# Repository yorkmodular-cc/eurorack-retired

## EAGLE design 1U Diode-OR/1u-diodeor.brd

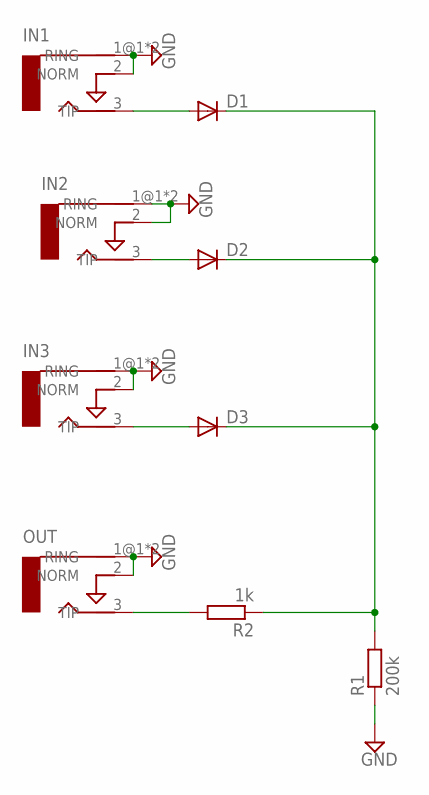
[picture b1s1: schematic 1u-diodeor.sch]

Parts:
D1, D2, D3: DIODE-SOD123; SOD123
IN1, IN2, IN3: AUDIO-JACKERTHENVAR; ERTHENVAR-JACK
OUT: AUDIO-JACKERTHENVAR; ERTHENVAR-JACK
R1: 200k; R0805
R2: 1k; R0805

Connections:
GND: IN1.1@1 (RING), IN1.1@2 (RING), IN1.2 (NORM), IN2.1@1 (RING), IN2.1@2 (RING), IN2.2 (NORM), IN3.1@1 (RING), IN3.1@2 (RING), IN3.2 (NORM), OUT.1@1 (RING), OUT.1@2 (RING), OUT.2 (NORM), R1.1
unnamed: D1.A, IN1.3 (TIP)
unnamed: D2.A, IN2.3 (TIP)
unnamed: D3.A, IN3.3 (TIP)
unnamed: D1.C, D2.C, D3.C, R1.2, R2.1
unnamed: OUT.3 (TIP), R2.2

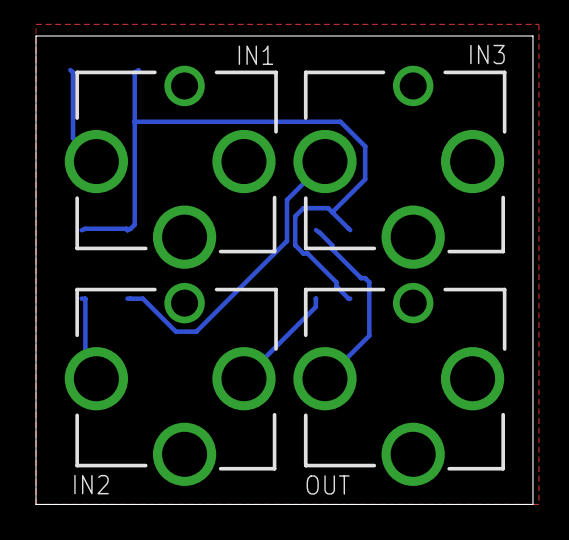
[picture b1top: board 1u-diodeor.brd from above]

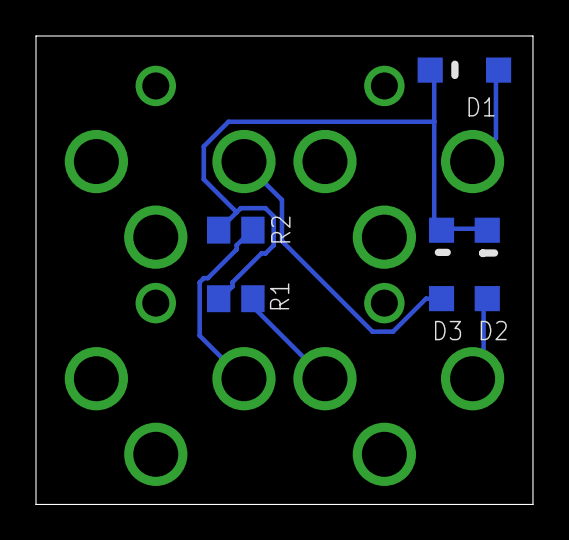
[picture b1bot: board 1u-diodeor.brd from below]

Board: 2 copper layers, 27.6 x 26.0 mm, 9 parts (5 on the bottom side), 6 nets.

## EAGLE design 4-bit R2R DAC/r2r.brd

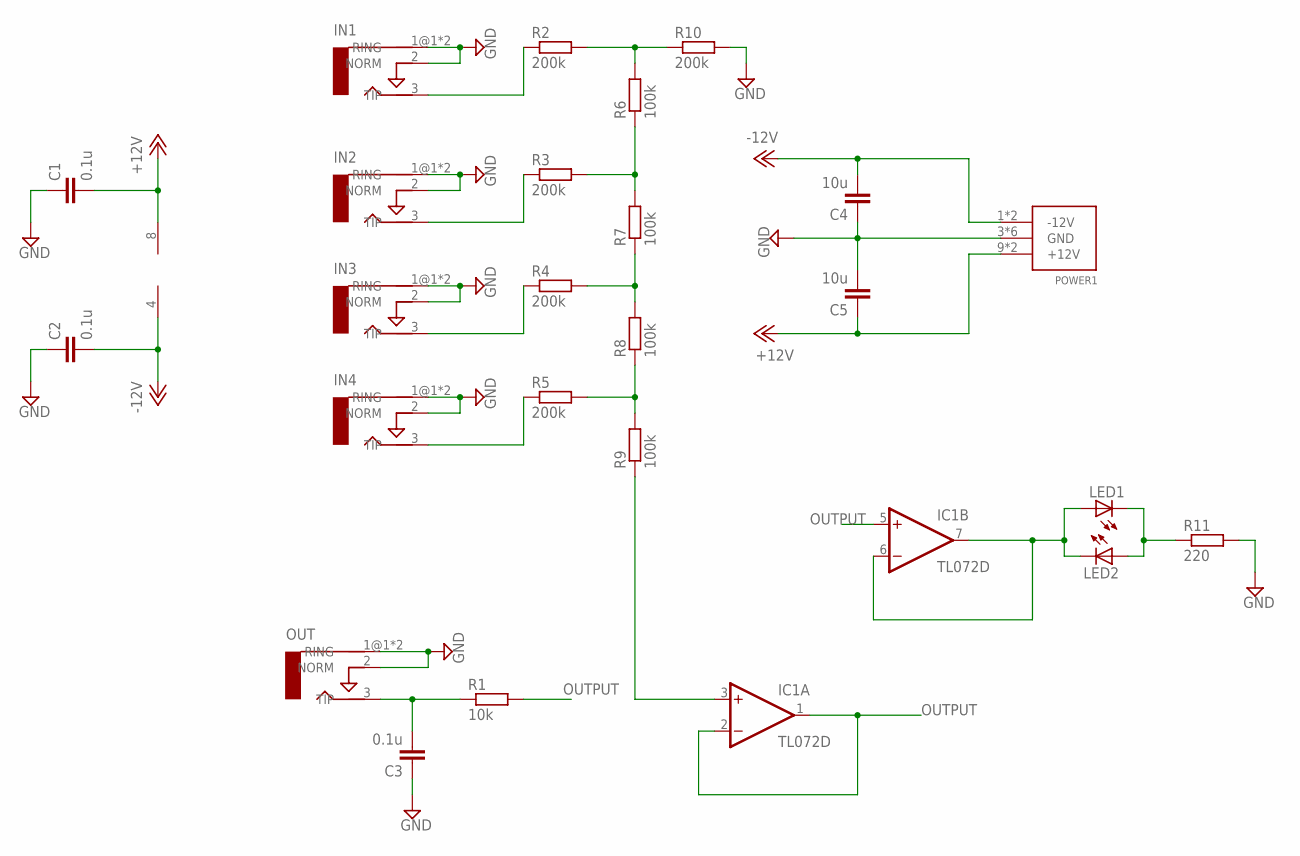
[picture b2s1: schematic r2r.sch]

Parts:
C1, C2, C3: 0.1u; C0805
C4, C5: 10u; C0805
IC1: TL072D; SO08
IN1, IN2, IN3, IN4: AUDIO-JACKERTHENVAR; ERTHENVAR-JACK
LED1, LED2: LEDCHIP-LED0805; CHIP-LED0805
OUT: AUDIO-JACKERTHENVAR; ERTHENVAR-JACK
POWER1: POWER_SIMPLE10; POWER_10
R1: 10k; R0805
R2, R3, R4, R5, R10: 200k; R0805
R6, R7, R8, R9: 100k; R0805
R11: 220; R0805

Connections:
+12V: C1.2, C5.1, IC1.8 (V+), POWER1.9 (+12V), POWER1.10 (+12V)
-12V: C2.2, C4.2, IC1.4 (V-), POWER1.1 (-12V), POWER1.2 (-12V)
GND: C1.1, C2.1, C3.1, C4.1, C5.2, IN1.1@1 (RING), IN1.1@2 (RING), IN1.2 (NORM), IN2.1@1 (RING), IN2.1@2 (RING), IN2.2 (NORM), IN3.1@1 (RING), IN3.1@2 (RING), IN3.2 (NORM), IN4.1@1 (RING), IN4.1@2 (RING), IN4.2 (NORM), OUT.1@1 (RING), OUT.1@2 (RING), OUT.2 (NORM), POWER1.3 (GND), POWER1.4 (GND), POWER1.5 (GND), POWER1.6 (GND), POWER1.7 (GND), POWER1.8 (GND), R10.2, R11.2
unnamed: IN1.3 (TIP), R2.1
unnamed: R2.2, R6.2, R10.1
unnamed: IN2.3 (TIP), R3.1
unnamed: R3.2, R6.1, R7.2
unnamed: IC1.3 (+IN), R9.1
unnamed: R5.2, R8.1, R9.2
unnamed: R4.2, R7.1, R8.2
unnamed: IN3.3 (TIP), R4.1
unnamed: IN4.3 (TIP), R5.1
unnamed: LED1.C, LED2.A, R11.1
unnamed: C3.2, OUT.3 (TIP), R1.1
unnamed: IC1.6 (-IN), IC1.7 (OUT), LED1.A, LED2.C
OUTPUT: IC1.1 (OUT), IC1.2 (-IN), IC1.5 (+IN), R1.2

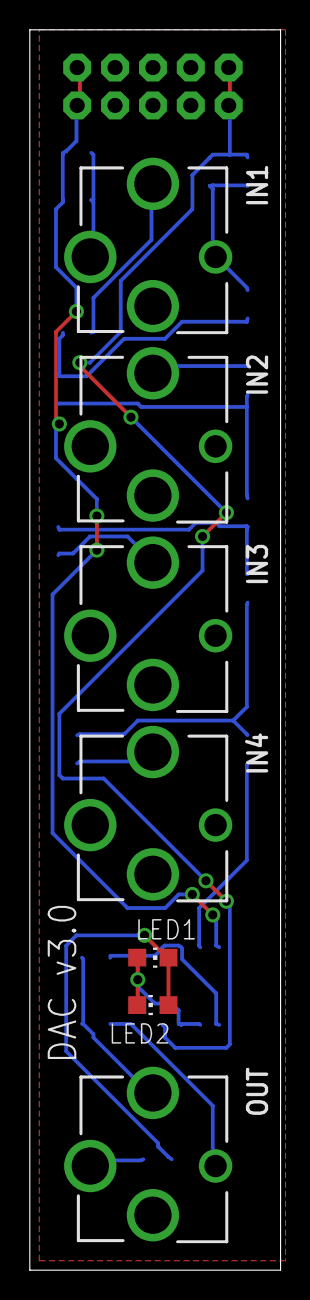
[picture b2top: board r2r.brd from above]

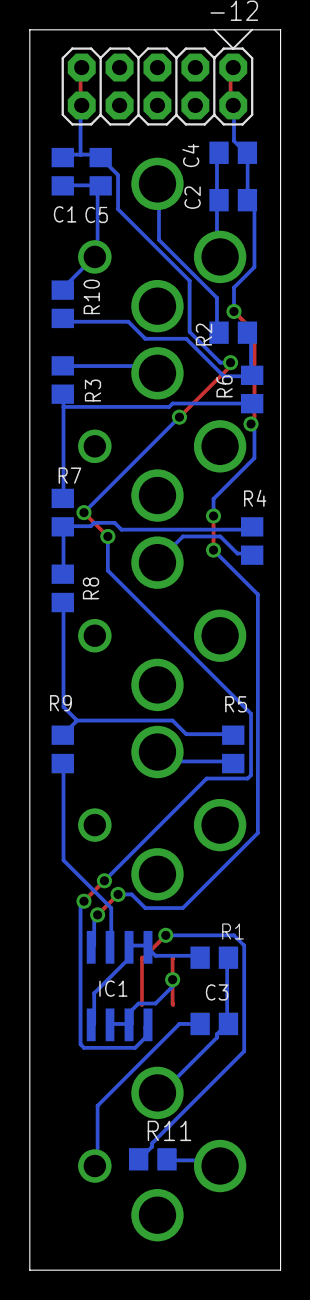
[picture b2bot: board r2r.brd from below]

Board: 2 copper layers, 16.8 x 83.2 mm, 25 parts (18 on the bottom side), 16 nets.

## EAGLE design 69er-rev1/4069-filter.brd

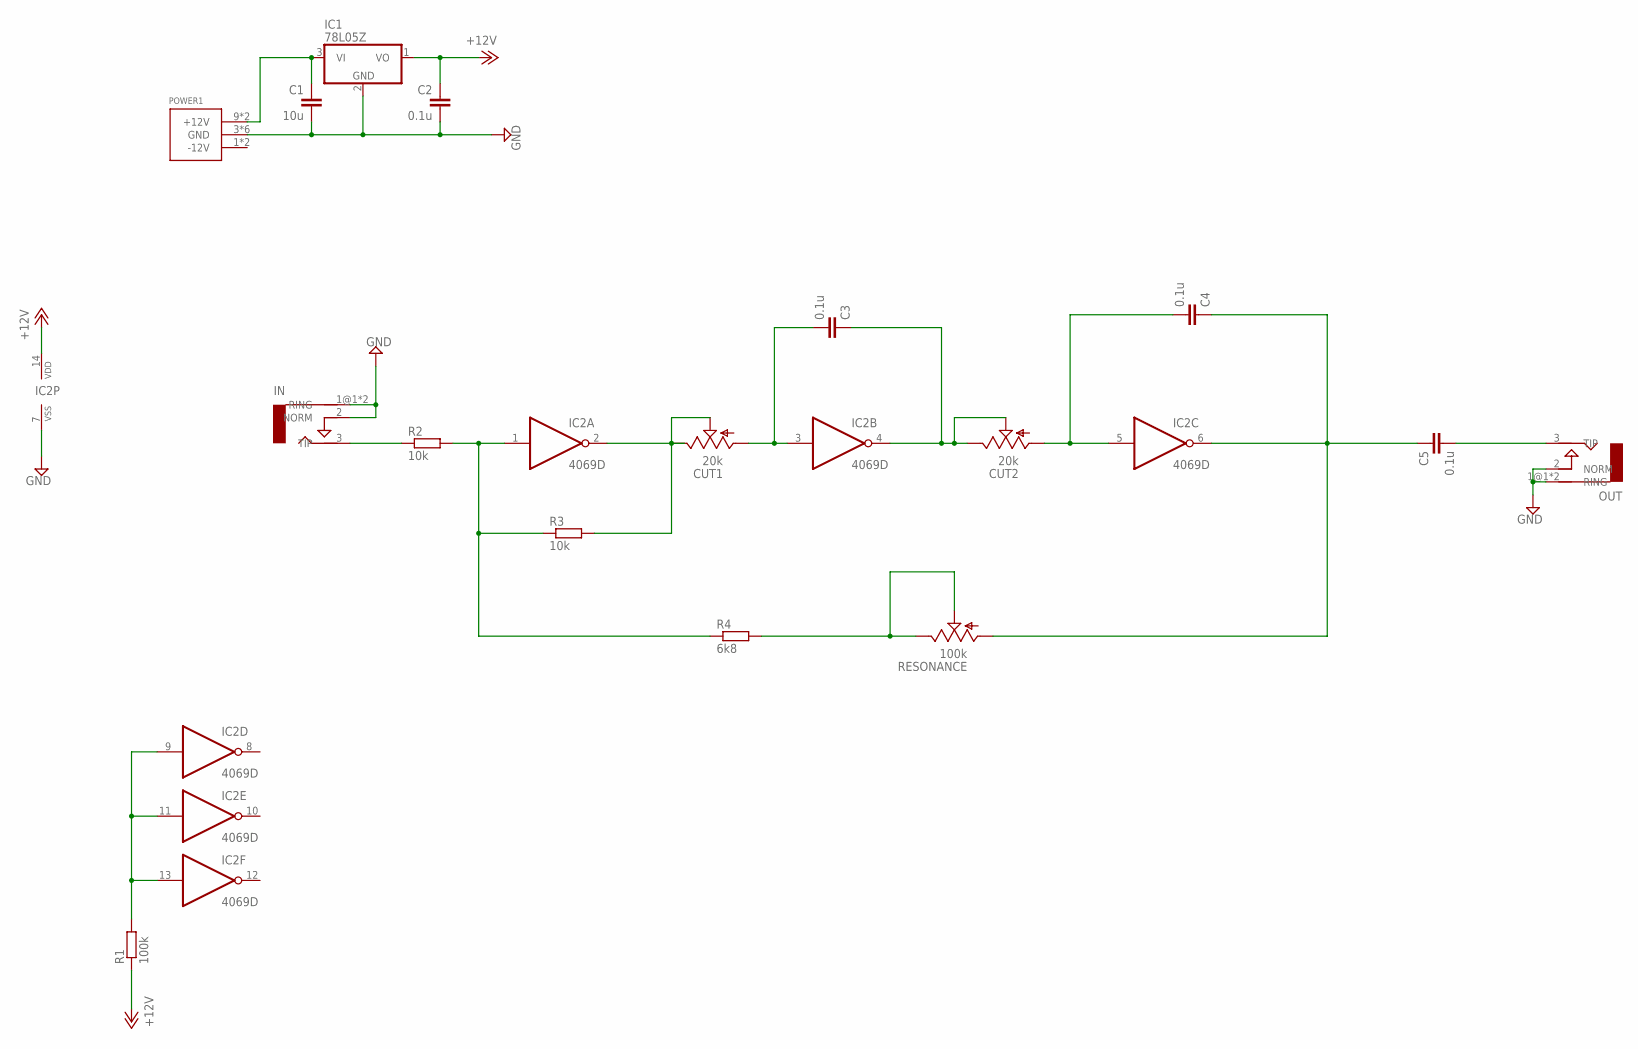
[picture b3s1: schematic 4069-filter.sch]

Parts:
C1: 10u; C0805
C2, C3, C4, C5: 0.1u; C0805
CUT1, CUT2: 20k; 9MM_SNAP-IN_POT
IC1: 78L05Z; TO92
IC2: 4069D; SO14
IN: AUDIO-JACKERTHENVAR; ERTHENVAR-JACK
OUT: AUDIO-JACKERTHENVAR; ERTHENVAR-JACK
POWER1: POWER_SIMPLE10; POWER_10
R1: 100k; R0805
R2, R3: 10k; R0805
R4: 6k8; R0805
RESONANCE: 100k; 9MM_SNAP-IN_POT

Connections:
+12V: C2.1, IC1.1 (VO), IC2.14 (VDD), R1.1
FILTER_OUT1: C3.1, CUT2.2 (S), CUT2.3 (E), IC2.4 (O)
FILTER_OUT2: C4.1, C5.1, IC2.6 (O), RESONANCE.1 (A)
GND: C1.2, C2.2, IC1.2 (GND), IC2.7 (VSS), IN.1@1 (RING), IN.1@2 (RING), IN.2 (NORM), OUT.1@1 (RING), OUT.1@2 (RING), OUT.2 (NORM), POWER1.3 (GND), POWER1.4 (GND), POWER1.5 (GND), POWER1.6 (GND), POWER1.7 (GND), POWER1.8 (GND)
IN: IN.3 (TIP), R2.1
unnamed: C5.2, OUT.3 (TIP)
unnamed: IC2.9 (I), IC2.11 (I), IC2.13 (I), R1.2
unnamed: C1.1, IC1.3 (VI), POWER1.9 (+12V), POWER1.10 (+12V)
unnamed: C3.2, CUT1.1 (A), IC2.3 (I)
unnamed: C4.2, CUT2.1 (A), IC2.5 (I)
unnamed: R4.2, RESONANCE.2 (S), RESONANCE.3 (E)
unnamed: CUT1.2 (S), CUT1.3 (E), IC2.2 (O), R3.2
unnamed: IC2.1 (I), R2.2, R3.1, R4.1

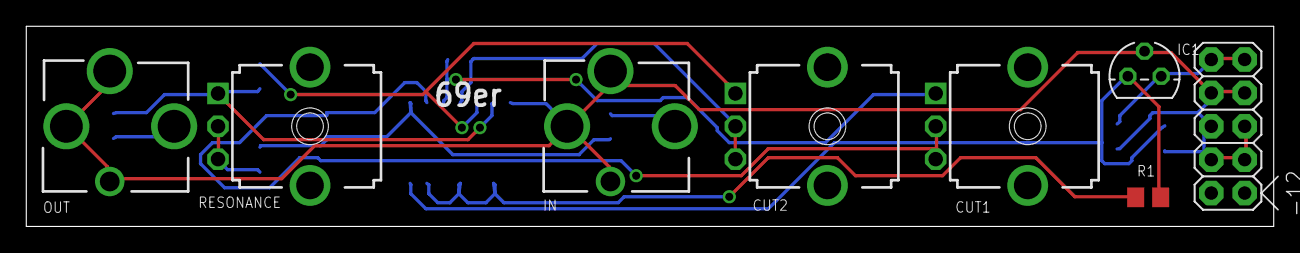
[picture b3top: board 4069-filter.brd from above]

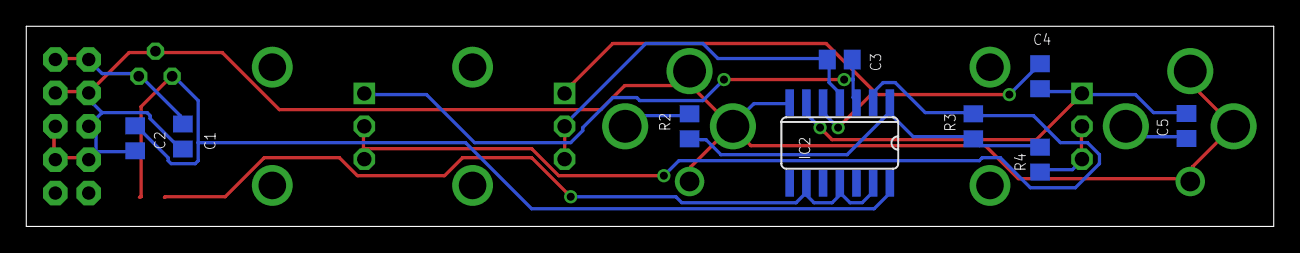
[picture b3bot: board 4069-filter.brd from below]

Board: 2 copper layers, 94.9 x 15.2 mm, 17 parts (9 on the bottom side), 13 nets.

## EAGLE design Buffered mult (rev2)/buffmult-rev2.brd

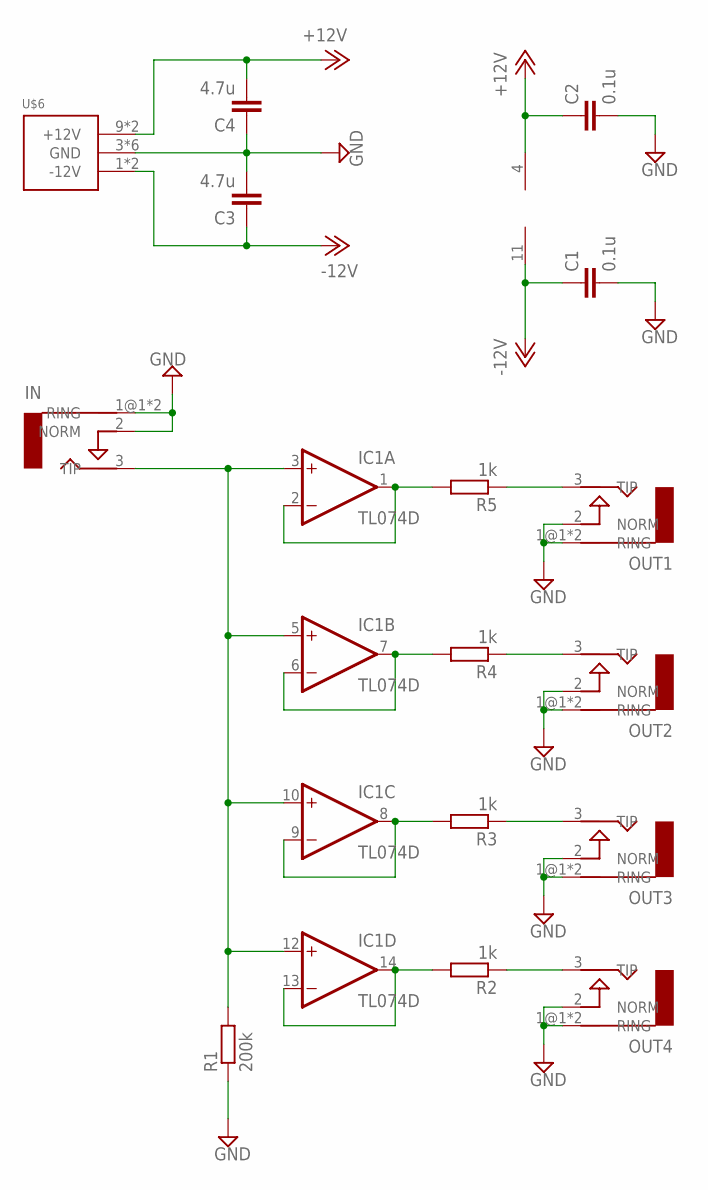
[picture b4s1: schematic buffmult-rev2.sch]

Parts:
C1, C2: 0.1u; C0805
C3, C4: 4.7u; C0805
IC1: TL074D; SO14
IN: AUDIO-JACKERTHENVAR; ERTHENVAR-JACK
OUT1, OUT2, OUT3, OUT4: AUDIO-JACKERTHENVAR; ERTHENVAR-JACK
R1: 200k; R0805
R2, R3, R4, R5: 1k; R0805
U$6: POWER_SIMPLE10; POWER_10

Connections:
+12V: C2.1, C4.2, IC1.4 (V+), U$6.9 (+12V), U$6.10 (+12V)
-12V: C1.1, C3.1, IC1.11 (V-), U$6.1 (-12V), U$6.2 (-12V)
GND: C1.2, C2.2, C3.2, C4.1, IN.1@1 (RING), IN.1@2 (RING), IN.2 (NORM), OUT1.1@1 (RING), OUT1.1@2 (RING), OUT1.2 (NORM), OUT2.1@1 (RING), OUT2.1@2 (RING), OUT2.2 (NORM), OUT3.1@1 (RING), OUT3.1@2 (RING), OUT3.2 (NORM), OUT4.1@1 (RING), OUT4.1@2 (RING), OUT4.2 (NORM), R1.1, U$6.3 (GND), U$6.4 (GND), U$6.5 (GND), U$6.6 (GND), U$6.7 (GND), U$6.8 (GND)
unnamed: IC1.1 (OUT), IC1.2 (-IN), R5.2
unnamed: IC1.6 (-IN), IC1.7 (OUT), R4.2
unnamed: IC1.8 (OUT), IC1.9 (-IN), R3.2
unnamed: IC1.13 (-IN), IC1.14 (OUT), R2.2
unnamed: IC1.3 (+IN), IC1.5 (+IN), IC1.10 (+IN), IC1.12 (+IN), IN.3 (TIP), R1.2
unnamed: OUT4.3 (TIP), R2.1
unnamed: OUT3.3 (TIP), R3.1
unnamed: OUT2.3 (TIP), R4.1
unnamed: OUT1.3 (TIP), R5.1

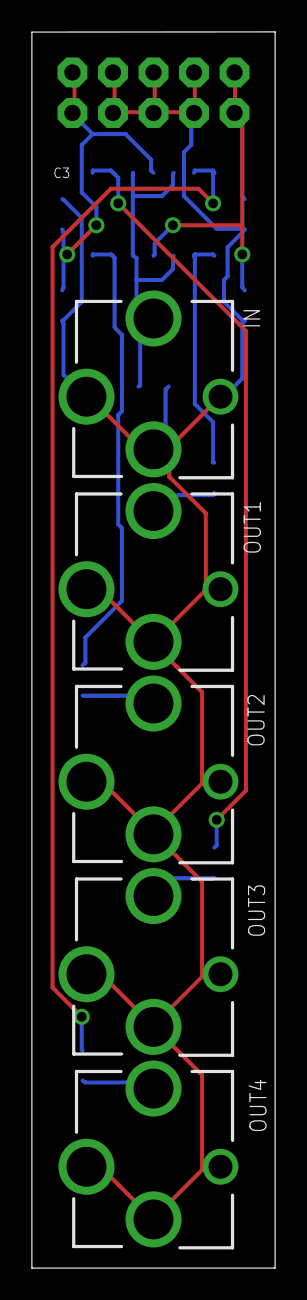
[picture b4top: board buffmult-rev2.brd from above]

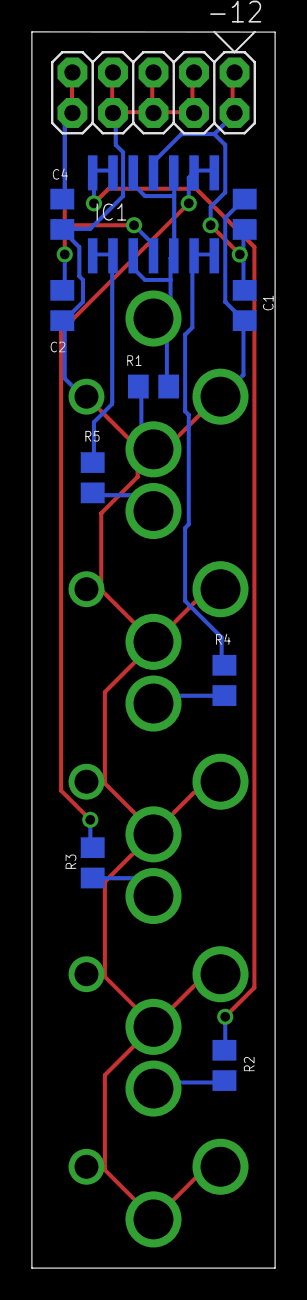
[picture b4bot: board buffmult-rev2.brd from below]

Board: 2 copper layers, 15.2 x 77.5 mm, 16 parts (11 on the bottom side), 12 nets.

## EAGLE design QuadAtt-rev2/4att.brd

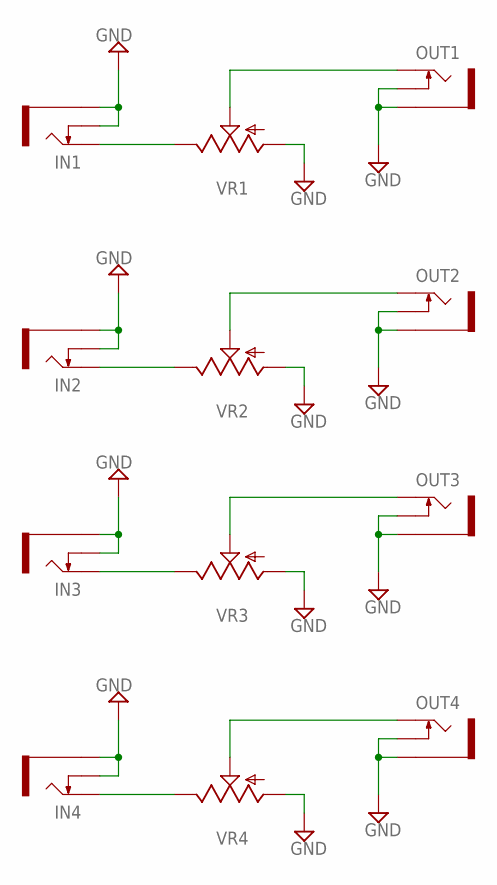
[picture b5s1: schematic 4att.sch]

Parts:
IN1, IN2, IN3, IN4: THONKICONNNEW; WQP-PJ301M-12_JACK
OUT1, OUT2, OUT3, OUT4: THONKICONNNEW; WQP-PJ301M-12_JACK
VR1, VR2, VR3, VR4: 9MM_SNAP-IN_POT_; 9MM_SNAP-IN_POT

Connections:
GND: IN1.P$2_SWITCH (SWITCH), IN1.P$3_SLEEVE (SLEEVE), IN2.P$2_SWITCH (SWITCH), IN2.P$3_SLEEVE (SLEEVE), IN3.P$2_SWITCH (SWITCH), IN3.P$3_SLEEVE (SLEEVE), IN4.P$2_SWITCH (SWITCH), IN4.P$3_SLEEVE (SLEEVE), OUT1.P$2_SWITCH (SWITCH), OUT1.P$3_SLEEVE (SLEEVE), OUT2.P$2_SWITCH (SWITCH), OUT2.P$3_SLEEVE (SLEEVE), OUT3.P$2_SWITCH (SWITCH), OUT3.P$3_SLEEVE (SLEEVE), OUT4.P$2_SWITCH (SWITCH), OUT4.P$3_SLEEVE (SLEEVE), VR1.1 (A), VR2.1 (A), VR3.1 (A), VR4.1 (A)
unnamed: IN1.P$1_TIP (TIP), VR1.3 (E)
unnamed: OUT1.P$1_TIP (TIP), VR1.2 (S)
unnamed: IN2.P$1_TIP (TIP), VR2.3 (E)
unnamed: OUT2.P$1_TIP (TIP), VR2.2 (S)
unnamed: IN3.P$1_TIP (TIP), VR3.3 (E)
unnamed: OUT3.P$1_TIP (TIP), VR3.2 (S)
unnamed: IN4.P$1_TIP (TIP), VR4.3 (E)
unnamed: OUT4.P$1_TIP (TIP), VR4.2 (S)

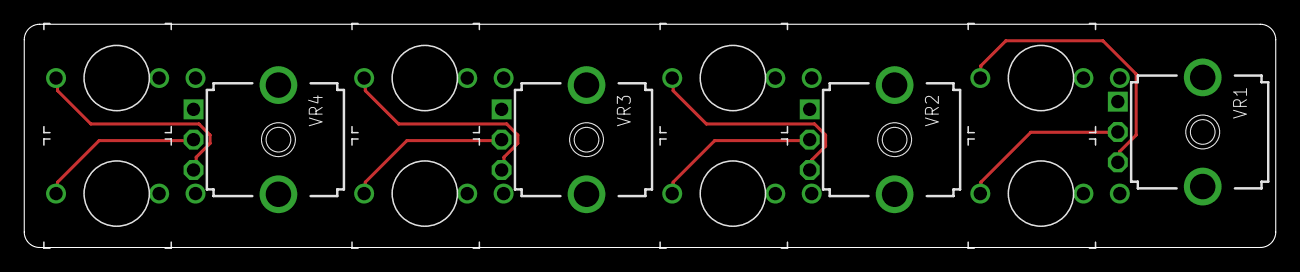
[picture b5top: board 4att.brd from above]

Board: 2 copper layers, 103.2 x 18.4 mm, 12 parts (0 on the bottom side), 9 nets.

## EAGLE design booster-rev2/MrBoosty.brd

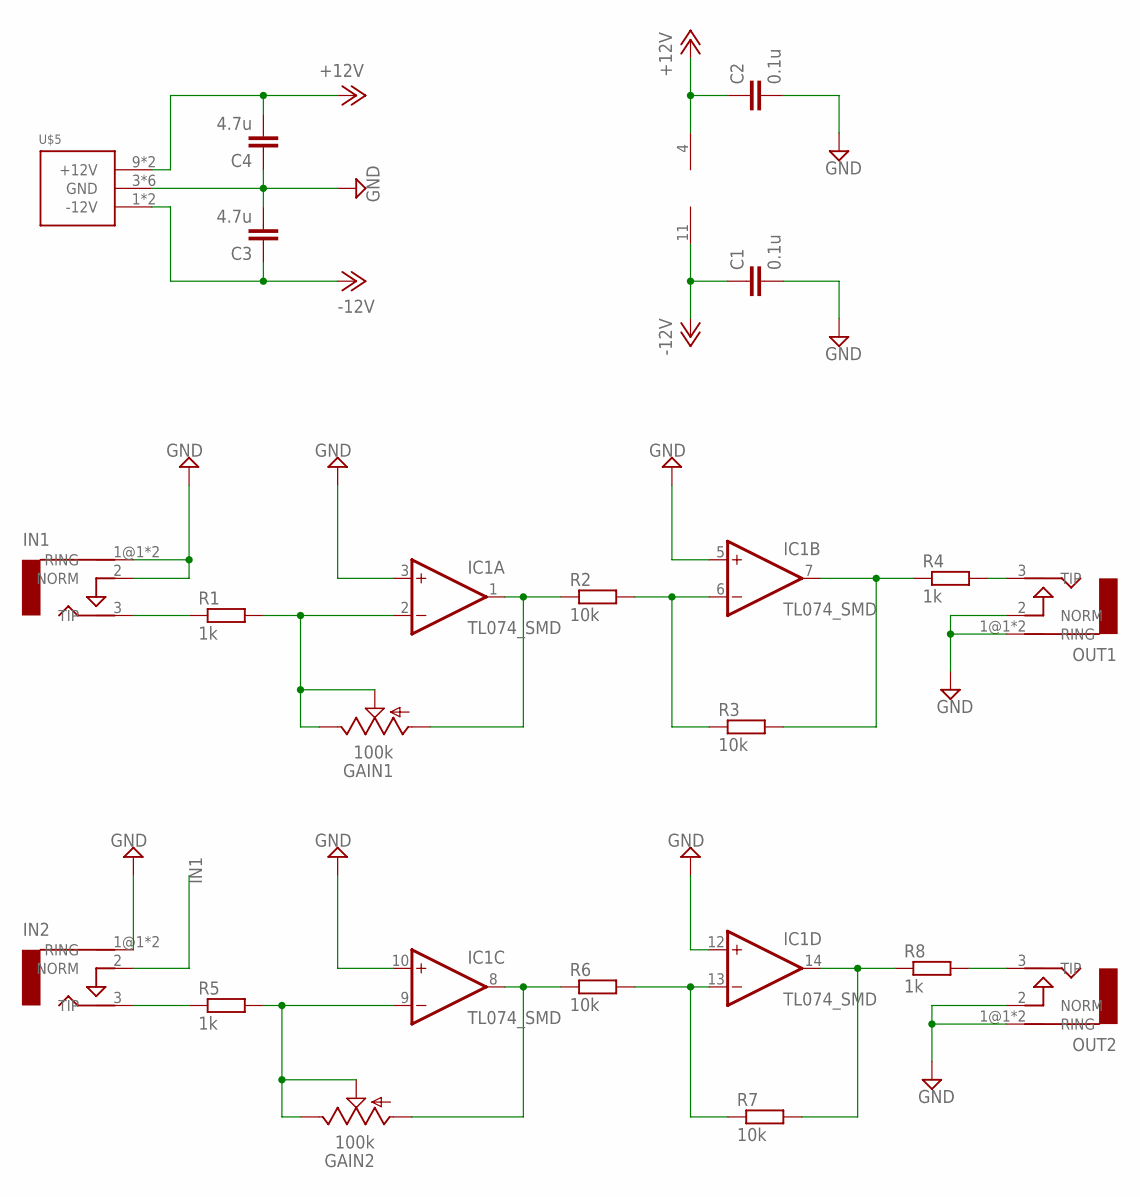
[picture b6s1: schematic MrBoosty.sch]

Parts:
C1, C2: 0.1u; C0805
C3, C4: 4.7u; C0805
GAIN1, GAIN2: 100k; 9MM_SNAP-IN_POT
IC1: TL074_SMD; SO14
IN1, IN2: AUDIO-JACKERTHENVAR; ERTHENVAR-JACK
OUT1, OUT2: AUDIO-JACKERTHENVAR; ERTHENVAR-JACK
R1, R4, R5, R8: 1k; R0805
R2, R3, R6, R7: 10k; R0805
U$5: POWER_SIMPLE10; POWER_10

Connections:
+12V: C2.1, C4.2, IC1.4 (V+), U$5.9 (+12V), U$5.10 (+12V)
-12V: C1.1, C3.1, IC1.11 (V-), U$5.1 (-12V), U$5.2 (-12V)
GND: C1.2, C2.2, C3.2, C4.1, IC1.3 (+IN), IC1.5 (+IN), IC1.10 (+IN), IC1.12 (+IN), IN1.1@1 (RING), IN1.1@2 (RING), IN1.2 (NORM), IN2.1@1 (RING), IN2.1@2 (RING), OUT1.1@1 (RING), OUT1.1@2 (RING), OUT1.2 (NORM), OUT2.1@1 (RING), OUT2.1@2 (RING), OUT2.2 (NORM), U$5.3 (GND), U$5.4 (GND), U$5.5 (GND), U$5.6 (GND), U$5.7 (GND), U$5.8 (GND)
IN1: IN1.3 (TIP), IN2.2 (NORM), R1.1
IN2: IN2.3 (TIP), R5.1
unnamed: GAIN1.2 (S), GAIN1.3 (E), IC1.2 (-IN), R1.2
unnamed: GAIN1.1 (A), IC1.1 (OUT), R2.1
unnamed: IC1.6 (-IN), R2.2, R3.1
unnamed: IC1.7 (OUT), R3.2, R4.1
unnamed: GAIN2.2 (S), GAIN2.3 (E), IC1.9 (-IN), R5.2
unnamed: GAIN2.1 (A), IC1.8 (OUT), R6.1
unnamed: IC1.13 (-IN), R6.2, R7.1
unnamed: IC1.14 (OUT), R7.2, R8.1
OUT1: OUT1.3 (TIP), R4.2
OUT2: OUT2.3 (TIP), R8.2

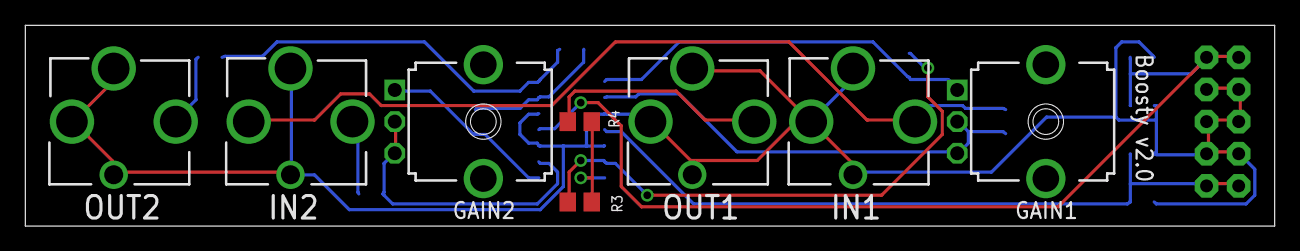
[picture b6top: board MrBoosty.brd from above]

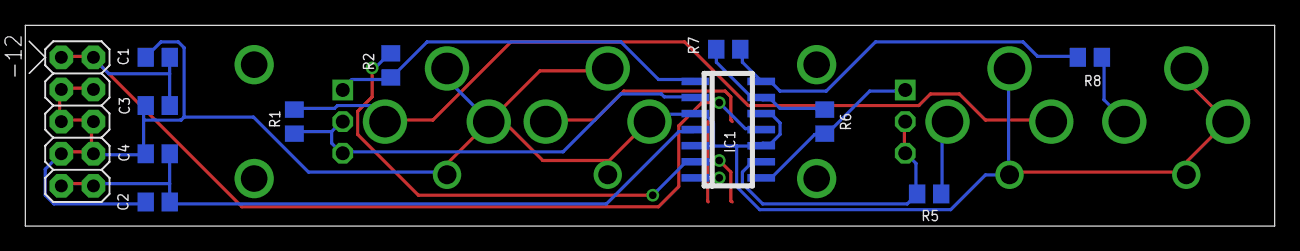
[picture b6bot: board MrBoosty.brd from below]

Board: 2 copper layers, 98.7 x 15.9 mm, 20 parts (12 on the bottom side), 15 nets.

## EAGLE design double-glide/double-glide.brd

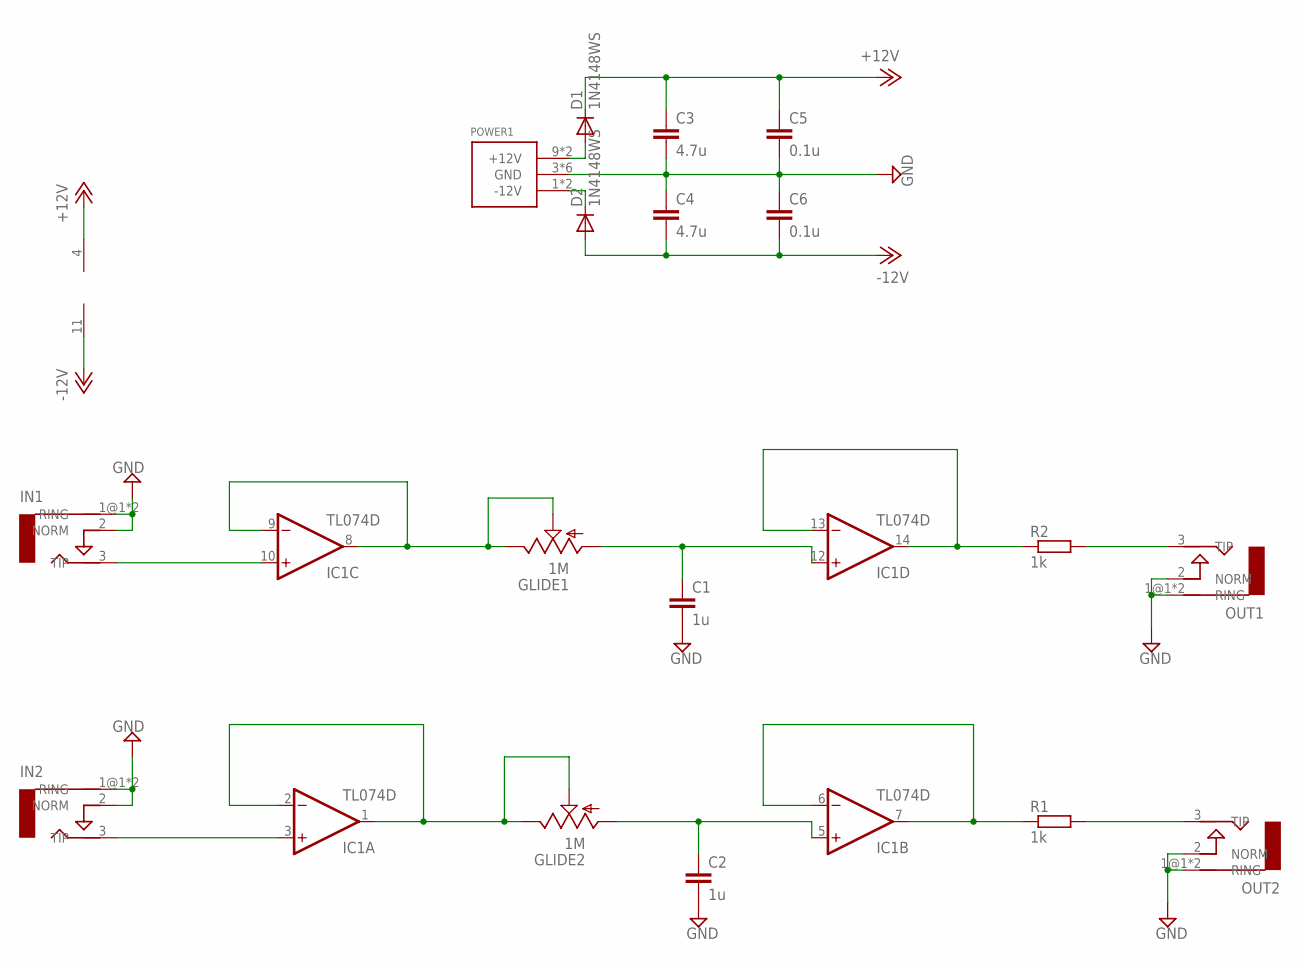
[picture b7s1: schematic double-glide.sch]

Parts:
C1, C2: 1u; C0805
C3, C4: 4.7u; C0805
C5, C6: 0.1u; C0805
D1, D2: 1N4148WS; SOD323-W
GLIDE1, GLIDE2: 1M; 9MM_SNAP-IN_POT
IC1: TL074D; SO14
IN1, IN2: AUDIO-JACKERTHENVAR; ERTHENVAR-JACK
OUT1, OUT2: AUDIO-JACKERTHENVAR; ERTHENVAR-JACK
POWER1: POWER_SIMPLE10; POWER_10
R1, R2: 1k; R0805

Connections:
+12V: C3.1, C5.1, D1.C, IC1.4 (V+)
-12V: C4.2, C6.2, D2.A, IC1.11 (V-)
GND: C1.2, C2.2, C3.2, C4.1, C5.2, C6.1, IN1.1@1 (RING), IN1.1@2 (RING), IN1.2 (NORM), IN2.1@1 (RING), IN2.1@2 (RING), IN2.2 (NORM), OUT1.1@1 (RING), OUT1.1@2 (RING), OUT1.2 (NORM), OUT2.1@1 (RING), OUT2.1@2 (RING), OUT2.2 (NORM), POWER1.3 (GND), POWER1.4 (GND), POWER1.5 (GND), POWER1.6 (GND), POWER1.7 (GND), POWER1.8 (GND)
unnamed: GLIDE1.2 (S), GLIDE1.3 (E), IC1.8 (OUT), IC1.9 (-IN)
unnamed: IC1.13 (-IN), IC1.14 (OUT), R2.1
unnamed: GLIDE2.2 (S), GLIDE2.3 (E), IC1.1 (OUT), IC1.2 (-IN)
unnamed: IC1.6 (-IN), IC1.7 (OUT), R1.1
unnamed: IC1.3 (+IN), IN2.3 (TIP)
unnamed: IC1.10 (+IN), IN1.3 (TIP)
unnamed: C1.1, GLIDE1.1 (A), IC1.12 (+IN)
unnamed: C2.1, GLIDE2.1 (A), IC1.5 (+IN)
unnamed: OUT2.3 (TIP), R1.2
unnamed: D1.A, POWER1.9 (+12V), POWER1.10 (+12V)
unnamed: OUT1.3 (TIP), R2.2
unnamed: D2.C, POWER1.1 (-12V), POWER1.2 (-12V)

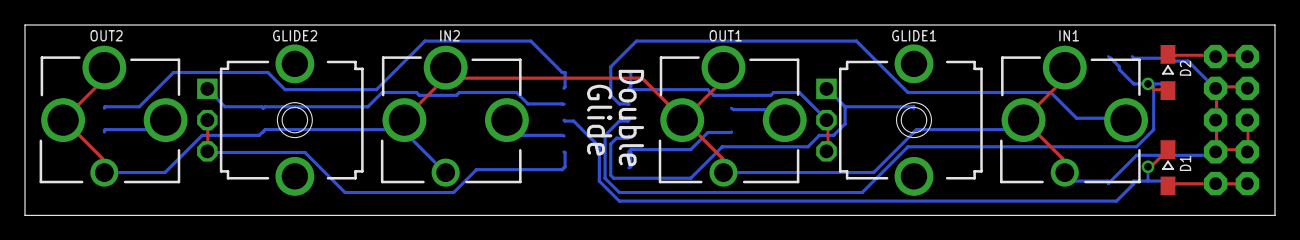
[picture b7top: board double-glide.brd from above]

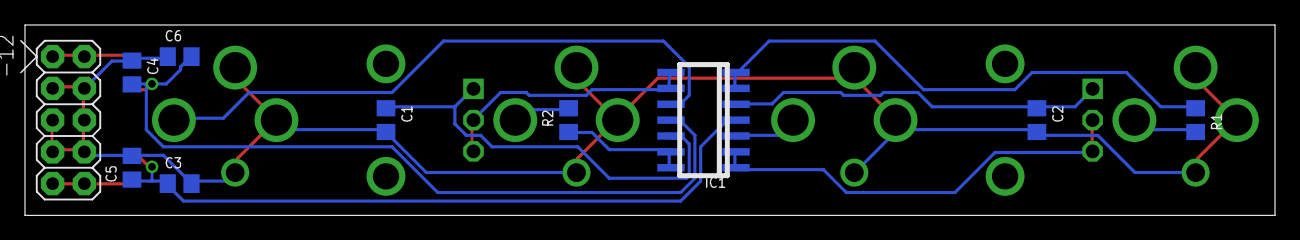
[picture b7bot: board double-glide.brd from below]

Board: 2 copper layers, 100.0 x 15.2 mm, 18 parts (10 on the bottom side), 15 nets.
